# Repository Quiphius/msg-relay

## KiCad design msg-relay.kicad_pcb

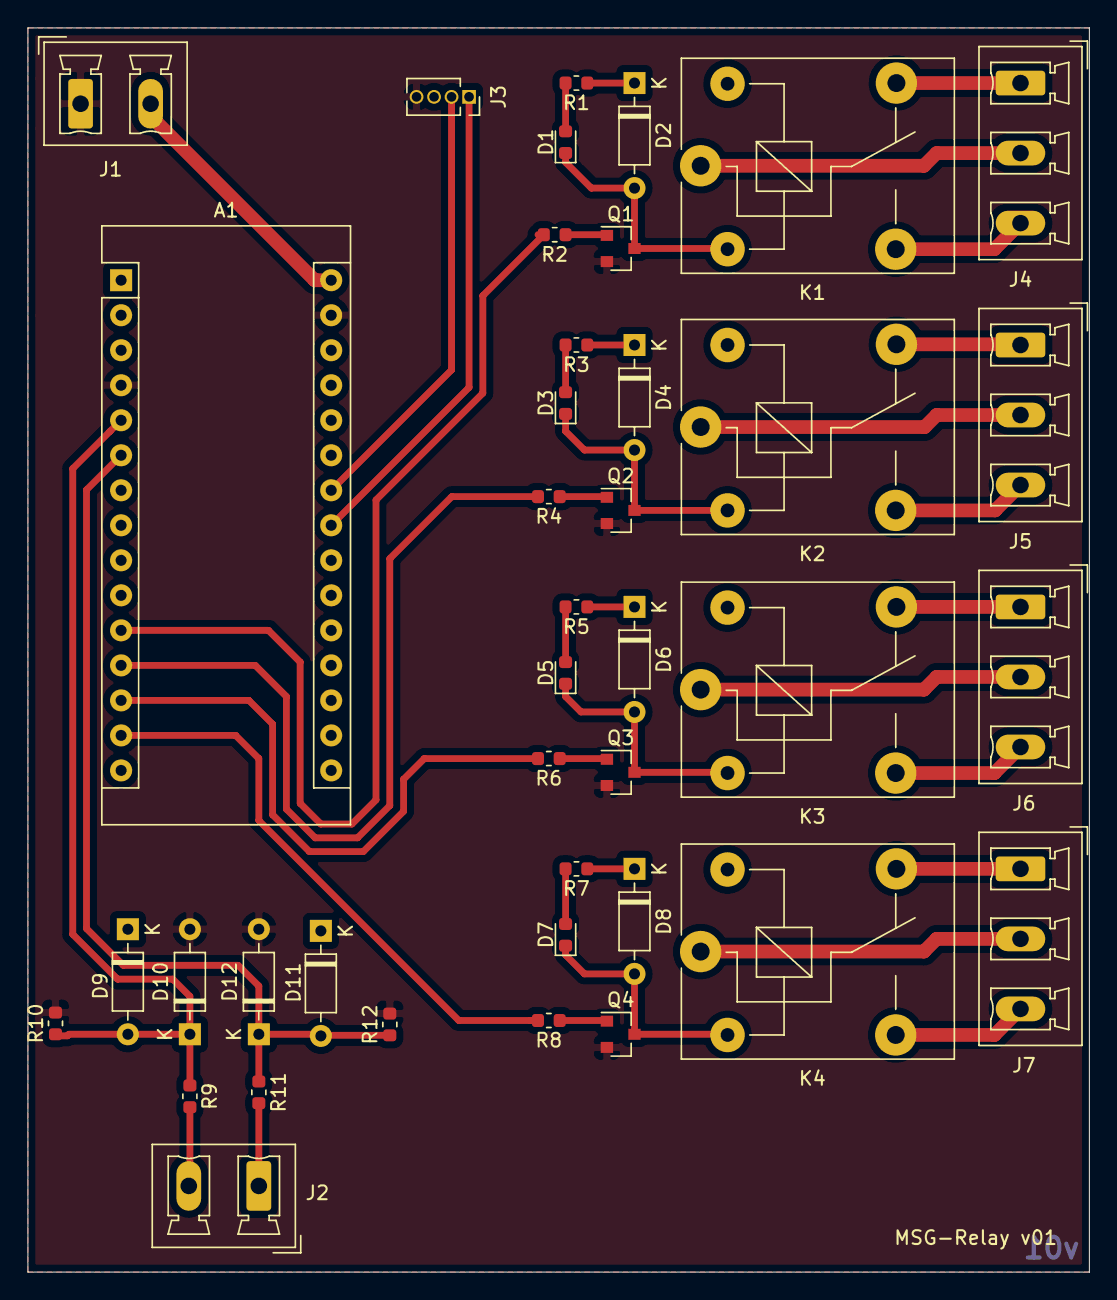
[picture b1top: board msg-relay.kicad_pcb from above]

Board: 2 copper layers, 77.0 x 90.2 mm, 40 parts (0 on the bottom side), 37 nets.

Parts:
A1: Arduino_Nano_v3.x; Arduino_Nano
D1, D3, D5, D7: LED; LED_0603_1608Metric
D2, D4, D6, D8: 1N4148; D_DO-35_SOD27_P7.62mm_Horizontal
D9, D10, D11, D12: BAT43; D_DO-35_SOD27_P7.62mm_Horizontal
J1, J2: Screw_Terminal_01x02; PhoenixContact_MCV_1,5_2-G-5.08_1x02_P5.08mm_Vertical
J3: Conn_01x04; PinSocket_1x04_P1.27mm_Vertical
J4, J5, J6, J7: Conn_01x03_Male; PhoenixContact_MCV_1,5_3-G-5.08_1x03_P5.08mm_Vertical
K1, K2, K3, K4: SANYOU_SRD_Form_C; Relay_SPDT_SANYOU_SRD_Series_Form_C
Q1, Q2, Q3, Q4: BC847; SOT-23
R1, R3, R5, R7: 1k; R_0603_1608Metric
R2, R4, R6, R8, R9, R10, R11, R12: 10k; R_0603_1608Metric

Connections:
+5V: A1.27, D2.1, D4.1, D6.1, D8.1, D9.1, D11.1, J3.3, K1.5, K2.5, K3.5, K4.5, R1.1, R3.1, R5.1, R7.1
+12V: A1.30, J1.2
/Input1/OUT: A1.5, D9.2, D10.1, R9.1, R10.1
/Input2/OUT: A1.6, D11.2, D12.1, R11.1, R12.1
GND: A1.4, A1.29, D10.2, D12.2, J1.1, J3.4, Q1.2, Q2.2, Q3.2, Q4.2, R10.2, R12.2
INPUT1: J2.2, R9.2
INPUT2: J2.1, R11.2
unnamed: D1.1, D2.2, K1.2, Q1.3
unnamed: D1.2, R1.2
unnamed: D3.1, D4.2, K2.2, Q2.3
unnamed: D3.2, R3.2
unnamed: D5.1, D6.2, K3.2, Q3.3
unnamed: D5.2, R5.2
unnamed: D7.1, D8.2, K4.2, Q4.3
unnamed: D7.2, R7.2
unnamed: J4.1, K1.4
unnamed: J4.2, K1.1
unnamed: J4.3, K1.3
unnamed: J5.1, K2.4
unnamed: J5.2, K2.1
unnamed: J5.3, K2.3
unnamed: J6.1, K3.4
unnamed: J6.2, K3.1
unnamed: J6.3, K3.3
unnamed: J7.1, K4.4
unnamed: J7.2, K4.1
unnamed: J7.3, K4.3
unnamed: Q1.1, R2.1
unnamed: Q2.1, R4.1
unnamed: Q3.1, R6.1
unnamed: Q4.1, R8.1
RELAY1: A1.11, R2.2
RELAY2: A1.12, R4.2
RELAY3: A1.13, R6.2
RELAY4: A1.14, R8.2
SCL: A1.24, J3.2
SDA: A1.23, J3.1

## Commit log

2019-04-28 Initial
2019-04-28 Added display and configuration over serial
2019-05-13 Some work on schema
2019-05-17 Split out relay to own schema
2019-05-19 Added README.md
2019-06-05 Added input module
2019-06-17 Made v01
2019-06-24 Added TODO and renamed file to avoid conflict
2019-06-26 Update times and loop delay
